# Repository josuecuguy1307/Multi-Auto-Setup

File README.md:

<div align="center">

<picture>
  <source media="(prefers-color-scheme: dark)" srcset="assets/brand/logo-dark.svg">
  
</picture>

**Your computers, working as a team. Your data, on your network.**

</div>

## Works with

Top row: the operating systems. Bottom row: the chats verified end to end so far. Every chat MAS can connect (Claude Desktop, Open WebUI, Muse Code, Claude Code, Codex, OpenCode) is listed under "What you can do with it".

<div align="center">
<picture><source media="(prefers-color-scheme: dark)" srcset="assets/readme/tile-macos-dark.svg"></picture>
<picture><source media="(prefers-color-scheme: dark)" srcset="assets/readme/tile-windows-dark.svg"></picture>
<picture><source media="(prefers-color-scheme: dark)" srcset="assets/readme/tile-linux-dark.svg"></picture>

<picture><source media="(prefers-color-scheme: dark)" srcset="assets/readme/tile-claude-desktop-dark.svg"></picture>
<picture><source media="(prefers-color-scheme: dark)" srcset="assets/readme/tile-open-webui-dark.svg"></picture>
<picture><source media="(prefers-color-scheme: dark)" srcset="assets/readme/tile-muse-code-dark.svg"></picture>
<picture><source media="(prefers-color-scheme: dark)" srcset="assets/readme/tile-claude-code-dark.svg"></picture>

<picture><source media="(prefers-color-scheme: dark)" srcset="assets/readme/tile-codex-dark.svg"></picture>
<picture><source media="(prefers-color-scheme: dark)" srcset="assets/readme/tile-opencode-dark.svg"></picture>
</div>

## Why MAS

You have several computers and several AIs. Today each AI sees one machine, and you are the glue. MAS is the control layer between **you**, **the AI** and **your machines**: one computer coordinates, the others join with your permission, a local model discovers and sets them up, and every decision that matters is yours. The model chooses its actions; code enforces the rules.

**Discover computers. Understand their capabilities. Prepare and equip their AI environments. Bring together models, agents, harnesses and specialized tools. Coordinate different machines securely as one system.**

## What you can do with it

- **Coding and software development** on the computer and coding harness that fit the task.
- **Software installation and environment setup**: analyze a machine, pick an option, approve the plan, install, verify.
- **CSV processing and data analysis** through the catalog task types for data work.
- **Financial reporting and report generation**: describe the work in your own words; the Recommendation Engine finds a suitable environment and asks you one question before anything is created.
- **Work from the chat you already use.** Connect it once (`mas connect`): Claude Desktop, Open WebUI, Muse Code, Claude Code, Codex and OpenCode reach the same MAS tools through MCP (stdio and streamable HTTP). You recognize your machines, answer questions and approve steps there; pairing codes and secrets never pass through a chat.

## Harnesses, matched to the work

A harness is the execution and tool-access environment an agent works inside. MAS keeps a catalog of environments and picks among them by rule, never by opinion:

| Work | Environments in the catalog |
|---|---|
| Coding | `codex`, `opencode`, `pi`, `claude-code`, `muse-code` |
| Local models and data work | `llamacpp-local` (text, code, summarize, extraction, data cleaning, numeric analysis) |
| Provider API | `meta-model-api` |
| General agent work | `goose`; domain skill packs such as the legal contract-review pack |

The **Recommendation Engine** explores tools, models, harnesses and environments for a kind of work: it names a default and an alternative, what is missing, and what could be installed (`mas_install_tool`) after you approve a plan. The **Router** then selects the harness, model, access and computer among the combinations your machines, permissions, privacy level and admission results allow, and records its reasoning. A confidential task is only ever routed to a combination measured on your own paired machines.

Models MAS can run with are profiles, not code: the local actor on each machine and the `muse-glimmer` / `muse-spark` profile names in `config/models.yaml`, with endpoints you supply. Which model runs where is decided from measured memory and fit, and shown to you before anything installs.

## Built with

MAS was built by two coding agents working during its construction, kept separate from the clients and models MAS operates: **Claude Code** (Claude Sonnet) and **Muse Code** (Meta Muse Wonder), including the local-model harness and Open WebUI integration work. **Claude Design** was used for design work, and smaller local Qwen models served as the in-harness actor during development and experiments. Orchestration, decisions, review and verification with the test and conformance suites: the owner, Josué.

## New in this release

| | What | Where to read it |
|---|---|---|
| <picture><source media="(prefers-color-scheme: dark)" srcset="assets/readme/symbols/coordinator-dark.svg"></picture> | **An interactive terminal for `mas`.** Home, Computers, Help, Questions and Progress in plain language, with clear errors and `mas preview` to try the screens with fake computers. Styled from the same single token source as every other surface, and meaning never depends on color alone. | `src/envrec_mas/tui.py`, `tests/test_tui.py` |
| <picture><source media="(prefers-color-scheme: dark)" srcset="assets/readme/symbols/network-dark.svg"></picture> | **One look for every surface.** The logo, colors and 27 pixel symbols come from one file (`src/envrec_style/tokens.json`); the README images, the terminal banner and the Open WebUI cards are drawn from it, and tests fail if one drifts. The banner adapts to the terminal (wide, narrow, compact; truecolor, 256 or 16 colors; shades with `NO_COLOR`; plain text with no escape codes when there is no terminal). | [docs/STYLE.md](docs/STYLE.md) |
| <picture><source media="(prefers-color-scheme: dark)" srcset="assets/readme/symbols/owner-dark.svg"></picture> | **A first-run menu.** `mas` with no arguments in a terminal shows the banner and a short menu for this computer only (role, service, connect Claude Desktop, announce a node). Each step runs the existing command through its own parser, which shows its plan and waits for your typed yes; the menu never answers for you. With no terminal it prints help and exits with code 2, with no prompt. | `src/envrec_mas/menu.py`, `tests/test_menu.py` |
| <picture><source media="(prefers-color-scheme: dark)" srcset="assets/readme/symbols/model-dark.svg"></picture> | **A recommender that checks itself by code.** For a task it has no answer for, it looks for candidate tools and models in public sources. A lead is kept only if code re-checks its license, whether it is archived, its last push, its stars and its domain tags from the page it came from; a rejected one is counted with a typed reason. The task type is chosen by independent picks, and when no two agree the owner is asked one question instead of a guess. A cloud second opinion is used only if you allowed cloud use, only through the node that holds the access, and never for confidential work. The first-run profile also asks which of your subscriptions may be used automatically. Leads stay hypotheses until measured. | [docs/RECOMMENDATION_SPEC.md](docs/RECOMMENDATION_SPEC.md), `tests/test_research_checks.py`, `tests/test_type_choice.py`, `tests/test_slots.py`, `tests/test_subscriptions.py` |
| <picture><source media="(prefers-color-scheme: dark)" srcset="assets/readme/symbols/script-dark.svg"></picture> | **One format for everything the harness says to you.** A title line with a symbol, short sections, numbered options you can answer with a number, a `Next:` line only when something is left to do. Three levels, `brief`, `normal` and `detailed` (`mas config verbosity LEVEL`, or ask in a chat); the commands of a plan or an approval are never shortened, and a test shows the content is the same at every level. A new conformance check (HA11) fails if text that only informs asks you to decide. | `src/envrec_harness/formatter.py`, `tests/test_formatter.py` |
| <picture><source media="(prefers-color-scheme: dark)" srcset="assets/readme/symbols/guard-dark.svg"></picture> | **A voice skill for the chat's own sentences** (`mas-voice`): answer in the person's language, briefly, ask with options, never touch fixed strings. It is handed to the chat when it connects. | `skills/mas-voice`, `tests/test_voice_skill.py` |

## How it works

<picture>
  <source media="(prefers-color-scheme: dark)" srcset="assets/readme/flow-dark.svg">
  
</picture>

| Stage | What goes in | What comes out |
|---|---|---|
| **1 Discover** | a computer on your own subnet | typed facts about it (hardware, system, programs, local AI runtimes), each with the probe that produced it |
| **2 Pair** | a 6-digit code shown on the coordinator, typed once on the new computer | pinned keys on both sides and your recorded yes; nothing else authorizes a computer |
| **3 Analyze** | the facts | what the machine can run, what is missing, options to choose from (you choose) |
| **4 Plan, with approval** | your pick | a plan with the exact commands, sizes and an undo, bound to a hash; you answer once, a changed plan asks again |
| **5 Route** | a task and its sensitivity level | a written rule picks a model and a machine among those allowed for that level; the reason is shown |
| **6 Log** | every event | an append-only, hash-chained log, each line tagged OWNER, MODEL, GUARD or SCRIPT (the router's choice is tagged ROUTER) |

### Features

| | Feature |
|---|---|
| <picture><source media="(prefers-color-scheme: dark)" srcset="assets/readme/symbols/network-dark.svg"></picture> | **One port.** The coordinator listens on one LAN port; nodes listen on none and always dial out. |
| <picture><source media="(prefers-color-scheme: dark)" srcset="assets/readme/symbols/paired-dark.svg"></picture> | **Pairing by key exchange.** A one-time code is the password of a SPAKE2 exchange; mutual TLS with pinned keys; signed messages. |
| <picture><source media="(prefers-color-scheme: dark)" srcset="assets/readme/symbols/model-dark.svg"></picture> | **A model decides, code guards.** One validated action per turn from a closed menu ([spec](docs/HARNESS_SPEC.md)). |
| <picture><source media="(prefers-color-scheme: dark)" srcset="assets/readme/symbols/approved-dark.svg"></picture> | **Approvals with an undo.** Every write shows the exact action and how to undo it, recorded first. |
| <picture><source media="(prefers-color-scheme: dark)" srcset="assets/readme/symbols/local-dark.svg"></picture> | **Local first.** Data stays on your machines unless you allow otherwise. |
| <picture><source media="(prefers-color-scheme: dark)" srcset="assets/readme/symbols/confidential-dark.svg"></picture> | **Sensitivity levels in code.** `public`, `internal`, `confidential`; a confidential task never goes to a cloud model. |
| <picture><source media="(prefers-color-scheme: dark)" srcset="assets/readme/symbols/guard-dark.svg"></picture> | **A conformance suite** (`conformance/`) that encodes the rules, including that a node opens no listening socket. |
| <picture><source media="(prefers-color-scheme: dark)" srcset="assets/readme/symbols/undone-dark.svg"></picture> | **Undo.** A finished setup can be undone as its own approved run. |

## Safety model

- **Nodes open no ports.** The coordinator opens one LAN port (plus, only if you ask, a screen on this computer's loopback).
- **Pairing needs your code and your yes.** A code lives two minutes and allows one attempt.
- **Read-only by default.** Discovery reads; it writes nothing.
- **Every write is approved** with the exact command and its undo, a fresh approval each time.
- **Confidential never leaves your network.** Enforced when the router chooses and at the node's calls, not by a prompt. Cloud models and commercial harnesses count as cloud.
- **Key names only.** Secrets are entered in a hidden window on your computer, stored in the operating system's credential store, and never pass through a chat, a log or a prompt.
- **Your own machines only.** The software never changes a firewall, network profile or router setting; it tells you what to change.
- **Text from the world is data, never instructions.** Generated code runs only in a sandbox that fails closed, and you approve its exact hash before it touches a device.

Details: [docs/NETWORK_CONTRACT.md](docs/NETWORK_CONTRACT.md).

## Install

One installer per operating system. Each installs for one user, with no administrator rights, and installs this program only (no AI models). Nothing is signed, so download the script, read it, then run it. Details, uninstall, service, update and unpair: [docs/INSTALL.md](docs/INSTALL.md).

**macOS and Linux**

```bash
curl -fsSLO https://raw.githubusercontent.com/josuecuguy1307/Multi-Auto-Setup/main/install.sh
less install.sh
sh install.sh
```

**Windows 10 and 11 (PowerShell)**

```powershell
Invoke-WebRequest https://raw.githubusercontent.com/josuecuguy1307/Multi-Auto-Setup/main/install.ps1 -OutFile install.ps1
notepad install.ps1
powershell -ExecutionPolicy Bypass -File .\install.ps1
```

The installers download one pinned release and stop if its SHA-256 differs from the value written in the script. Afterwards: `mas join` on a node, `mas coordinator start --bind ADDRESS` on the coordinator, `mas service install` to start at sign-in, `mas update`, `mas unpair NODE`.

### From a source checkout

Python 3.11 or newer.

```bash
uv venv --python 3.13 .venv && uv pip install --python .venv/bin/python -e .
```

```bash
.venv/bin/python -m pytest conformance
```

## More

- **Harness App standard:** how a chat connects to the harness without being modified: [docs/HARNESS_APP_STANDARD.md](docs/HARNESS_APP_STANDARD.md).
- **Style:** the logo, colors and symbols: [docs/STYLE.md](docs/STYLE.md).
- **Licenses of what is used:** [THIRD_PARTY.md](THIRD_PARTY.md).
- **Portable device (branch `device/v0`):** the key with a physical approval button, its firmware, board and policy gate, what is simulated, emulated or design-only, and how to reproduce every check: [device/README.md](device/README.md).

## License

Licensed under the Apache License, Version 2.0. See LICENSE and NOTICE.

## Hackathon

Built for the Meta Global AI Developer Hackathon, Indie track.

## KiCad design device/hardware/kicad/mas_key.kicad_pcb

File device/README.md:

# MAS portable device (branch device/v0)

A portable device that carries its owner's AI (local model, agent harness, memory). Plugged into someone else's computer, and only
with that computer owner's permission, it connects the AI there without installing anything, inspects the machine read-only, and helps
set up MAS (Multi Auto Setup) on it, one approved write at a time with undo. A small key with a physical button is the only way to
approve a write: the limits live in the key's firmware and in the policy gate, not in the model. Source of truth: `MISSION.md`;
decisions: `DECISIONS.md`; where things stand: `ACCEPTANCE.md` (generated by the oracle) and `HANDOFF.md`.

## Honesty labels

Every result carries one label, in the code, in `ACCEPTANCE.md` and here:

- **SIMULATED**: a Python model on the development machine (for example the key's reference model, the host as a temporary folder).
- **EMULATED**: the real firmware or system running under an emulator or a virtual machine (QEMU, Renode, VMs).
- **DESIGN-ONLY**: a design that passed automatic checks but was never built (the PCB, the enclosure, the secure-boot plan).
- **REAL**: ran on real things (the repository itself, the oracle).

No board has been made. The fabrication files are stamped "NO FABRICAR sin revisión humana" and suffixed `_NO_FABRICAR`; the human
review list is `device/hardware/HUMAN_REVIEW_PCB.md`. Nothing here was tested on the actual key hardware.

**"No trace", defined (D-010).** The device never claims to leave no trace in the absolute. What it aims for, and what P2-ZEROTRACE
will measure, is: "Nothing installed: no service, driver, autostart, PATH change or file outside a declared temp dir removed on exit.
OS-generated residue is limited to an enumerated allowlist of classes" (USB device history, Prefetch and similar records the host's
operating system writes on its own).

## Where things are

| Path | What |
|---|---|
| `src/mas_device/approval.py` | Signed, single-use, expiring approval tokens (guardrail 3) |
| `src/mas_device/keymodel.py` | Python reference model of the key's firmware (SIMULATED) |
| `src/mas_device/gate.py` | The policy gate: the only code that writes to the host, with a fresh approval per write and a recorded undo |
| `src/mas_device/gated.py` | The gate as its own process, reached only through a fixed JSON-lines interface |
| `src/mas_device/log.py` | The append-only, hash-chained audit log |
| `device/firmware/` | The key's firmware in C (`device/firmware/README.md`), its secure-boot design (`device/firmware/SECURE_BOOT.md`) |
| `device/hardware/` | The key board as code: `device/hardware/design.py` is the source, `device/hardware/hwbuild.py` builds everything |
| `device/acceptance/criteria.yaml` | Every acceptance criterion: its tests, the files it covers, its label, its saboteurs |
| `device/tests/` | The tests behind every criterion |
| `device/evals/evaluator/` | Every independent evaluator report, verbatim |
| `scripts/device_accept.py` | The oracle: the only thing that writes `test-results.json` and the status table in `ACCEPTANCE.md` |

## Tools (versions used; reinstall if you change machines)

| Tool | Version | Install | Used by |
|---|---|---|---|
| Python venv | 3.13 | `uv venv .venv` then `uv pip install -e .` | everything |
| zig (`zig cc`) | 0.13.0 | `uv venv runs/toolchain --python 3.13` then `uv pip install --python runs/toolchain/Scripts/python.exe ziglang==0.13.0` | firmware host and emulator builds |
| QEMU (`qemu-system-arm`) | 11.1.0 | `winget install SoftwareFreedomConservancy.QEMU` | P4-FW-EMU |
| Renode (portable) | 1.17.0 | the official zip from github.com/renode/renode, release v1.17.0, unpacked in `runs/toolchain/renode/` | P4-FW-RENODE |
| KiCad (`kicad-cli`, its Python with pcbnew) | 10.0.8 | `winget install KiCad.KiCad` | P5-PCB |

Licenses for all of these are in `THIRD_PARTY.md`. `runs/` is git-ignored: tools and logs never enter the repository.

## Reproduce

One command runs every criterion and rewrites `test-results.json` and the table in `ACCEPTANCE.md`:

```
python scripts/device_accept.py run            # all criteria (about 40 minutes; the board rebuild is most of it)
python scripts/device_accept.py run --id P2-GATE
python scripts/device_accept.py status         # read-only
python scripts/device_accept.py verify         # read-only: fails if any recorded PASS is stale
python scripts/device_accept.py confirm        # the stop condition: clean tree, fresh worktree at HEAD, everything re-run
```

On Windows use `.venv/Scripts/python`; on POSIX `.venv/bin/python`. A criterion passes only if its tests pass, its minimum test count is
met and every saboteur (a deliberate break of the covered code) turns its tests red.

| Criterion | Label | What it shows | Needs |
|---|---|---|---|
| P1-HARNESS | REAL | the oracle treats skips and missing files as FAIL and detects stale results | Python |
| P1-DOCS | REAL | decisions, threat model, guardrail and PCB specs, advisor and reviewer advice are recorded | Python |
| P1-UNIT | SIMULATED | signed approvals, with an independent evaluator's PASS bound to the code's hash | Python |
| P2-GATE | SIMULATED | writes only with a fresh approval for the exact action; undo recorded first | Python |
| P2-LOG | SIMULATED | the audit log detects any edit, cut or reorder against a known head | Python |
| P2-GUARDRAILS | SIMULATED | a scripted malicious model gets zero violations of the ten guardrails | Python |
| P2-PORTABLE | EMULATED | one command (`sh launch.sh`) from a read-only medium in a clean Debian container with no Python and no network; the medium carries its own interpreter and is checked against its manifest; the profiler picks host or device compute from cgroup limits | Docker running; once: `python device/medium/mas_medium_build.py fetch` and `docker pull` of the pinned image |
| P2-ZEROTRACE | EMULATED | the D-010 three-arm diff over whole-filesystem snapshots of clean containers: the session leaves nothing, an approved write changes exactly its files, its undo returns to the session arm; a bad stick's installs are each caught | same as P2-PORTABLE (Docker running, medium cache) |
| P2-FLEET | EMULATED | three containers on an internal network: the host owner types JOIN <fleet>, one press for JOIN_FLEET (checked by the coordinator against the pinned key), one press per setup step, one per undo when leaving; a raw-frame sentinel sees nothing from the peers | same as P2-PORTABLE (Docker running, medium cache) |
| P2-MODEL | EMULATED | the local model answers from the read-only medium | not built yet; needs a local model |
| P2-MEMORY | SIMULATED | portable memory in the open `.mem` bundle format round-trips; at rest it is one scrypt + AES-256-GCM sealed file | Python |
| P2-PAIRING | SIMULATED | the gate accepts only the key paired with the medium (`pairing.json`); the owner sees the session terms at launch; MAS chat approvals absent from the device build | Python |
| P3-INSPECT | SIMULATED | inventory precision >= 0.95 and recall >= 0.90 on four fixture containers whose truth comes from independent tools (dpkg-query, uname, getconf, /sys/module, ioctl, /proc/partitions, the shell); exact on dpkg states, os-release quoting, kernel release and disks | same as P2-PORTABLE (Docker running, medium cache); raw scores in runs/eval/inspect-accuracy.json |
| P3-READONLY | EMULATED | one INSPECT_SESSION press, then a closed set of file-only collectors behind a path allowlist: zero writes by whole-filesystem diff, works on a read-only root, a network sentinel hears nothing, a host's link from an allowed name to a secret is refused; no MAS skill or scanner on the medium | same as P2-PORTABLE (Docker running, medium cache) |
| P3-REPORT | SIMULATED | three files per inspection in the device folder: the full JSON report and a bounded agent view, both checked against closed JSON Schemas (device validator and independent pydantic models agree on every mutation), and the owner's Markdown; hostile host text (terminal escapes, line breaks, bidi) is shown escaped; an invalid report is never written | Python |
| P3-NOCREDS | SIMULATED | hosts planted with secrets in every usual store (shadow, ssh, aws, .env, TLS key, git, browser, gcloud, process environ and cmdline) and inside allowed fields: none appears, raw or encoded, in any output; credential-like values are withheld whole; a stock Debian loses nothing | same as P2-PORTABLE (Docker running, medium cache) |
| P4-FW-HOST | SIMULATED | the firmware rejects replayed, altered and expired approvals; signs only after a press | zig |
| P4-FW-EMU | EMULATED | the same firmware in QEMU gives identical transcripts | zig, QEMU |
| P4-FW-RENODE | EMULATED | the same firmware in Renode gives identical transcripts | zig, Renode |
| P4-SECBOOT | DESIGN-ONLY | the secure-boot and lock design matches the firmware's assumptions | Python |
| P5-PCB | DESIGN-ONLY | ERC, DRC and fabrication checks green, board facts read through pcbnew | KiCad |
| P5-ENCLOSURE | DESIGN-ONLY | a parametric enclosure fits the board by automatic check | Python |
| P6-EVALS | REAL | evals reproducible with one command | not built yet |
| P6-REPO | REAL | this file, `THIRD_PARTY.md`, reproduction instructions | Python |
| P6-PAPER | REAL | the paper regenerates from raw results | not built yet |
| P0-SECRETS | REAL | no credentials anywhere in the tree or its history | git |

The board alone: `python device/hardware/hwbuild.py --out runs/hw/out` (5 to 10 minutes). The firmware alone:
`python device/firmware/build.py`.

## License

Software: see `LICENSE` and `NOTICE`. Hardware (the board and enclosure files): CERN-OHL-S-2.0, chosen by the owner on 2026-11-19 (`LICENSE-HARDWARE.md`, D-014). Earlier proposals (CERN-OHL-P-2.0) and the decision are recorded in `NEEDS_HUMAN.md` and D-014.

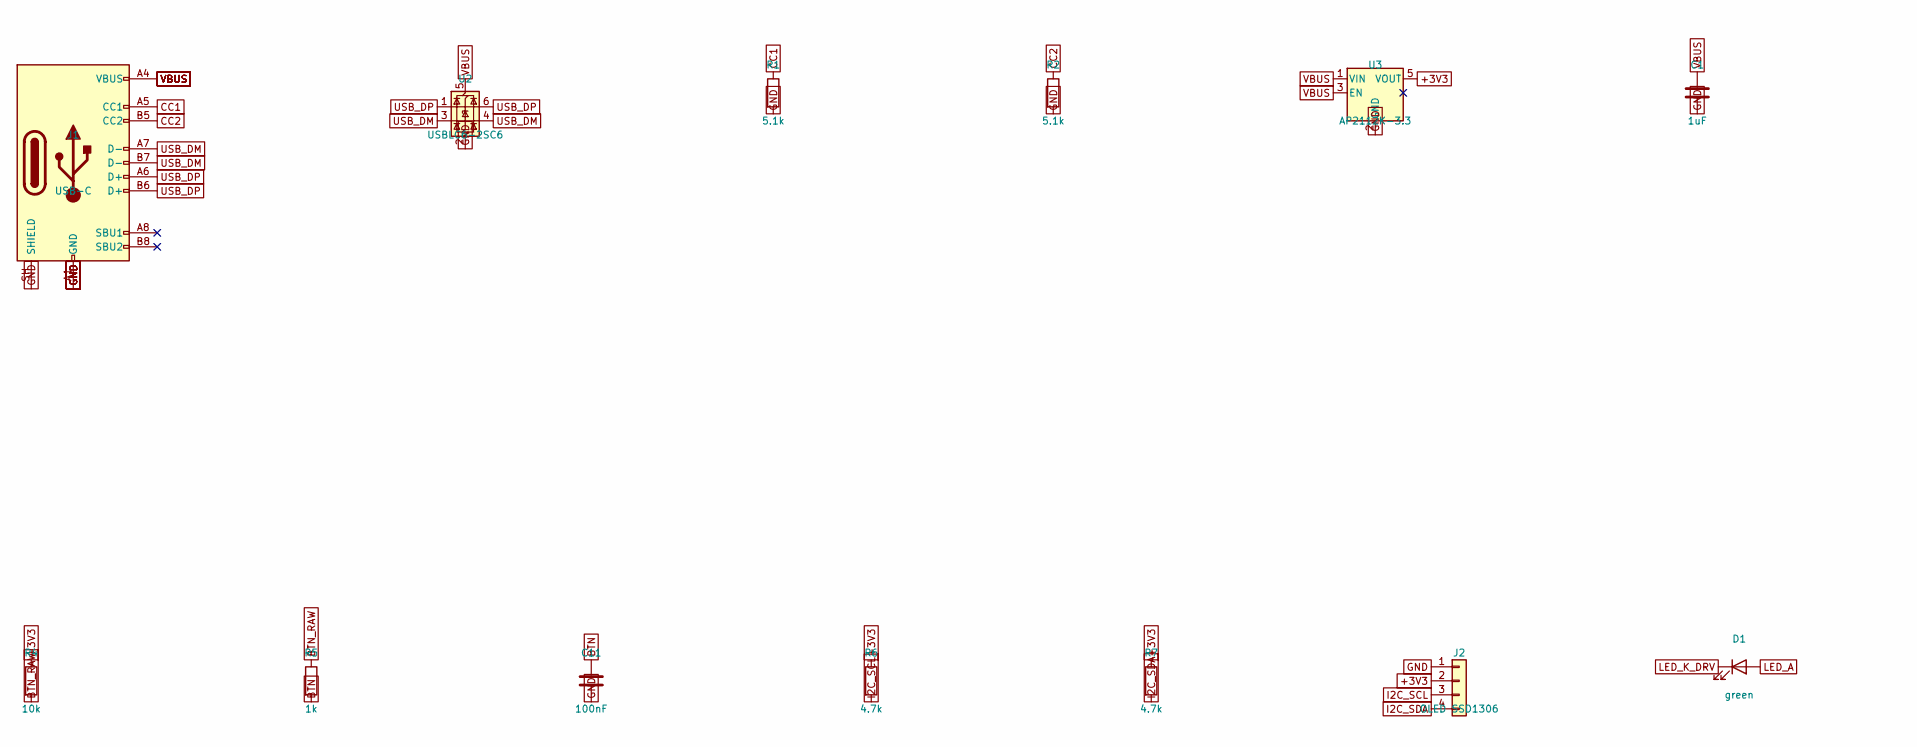
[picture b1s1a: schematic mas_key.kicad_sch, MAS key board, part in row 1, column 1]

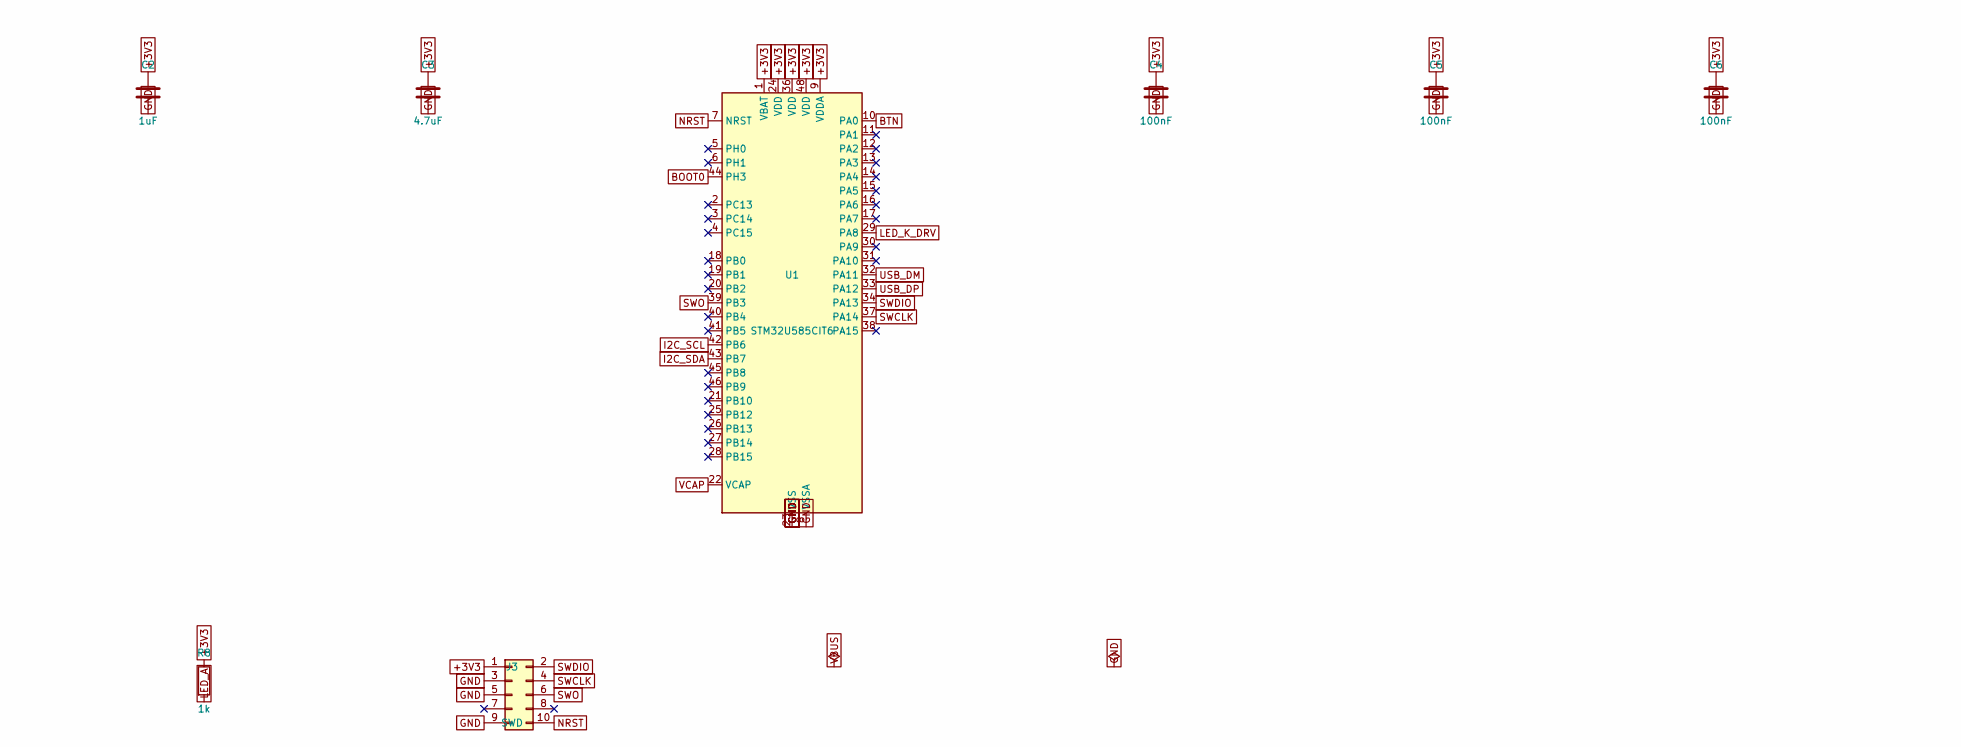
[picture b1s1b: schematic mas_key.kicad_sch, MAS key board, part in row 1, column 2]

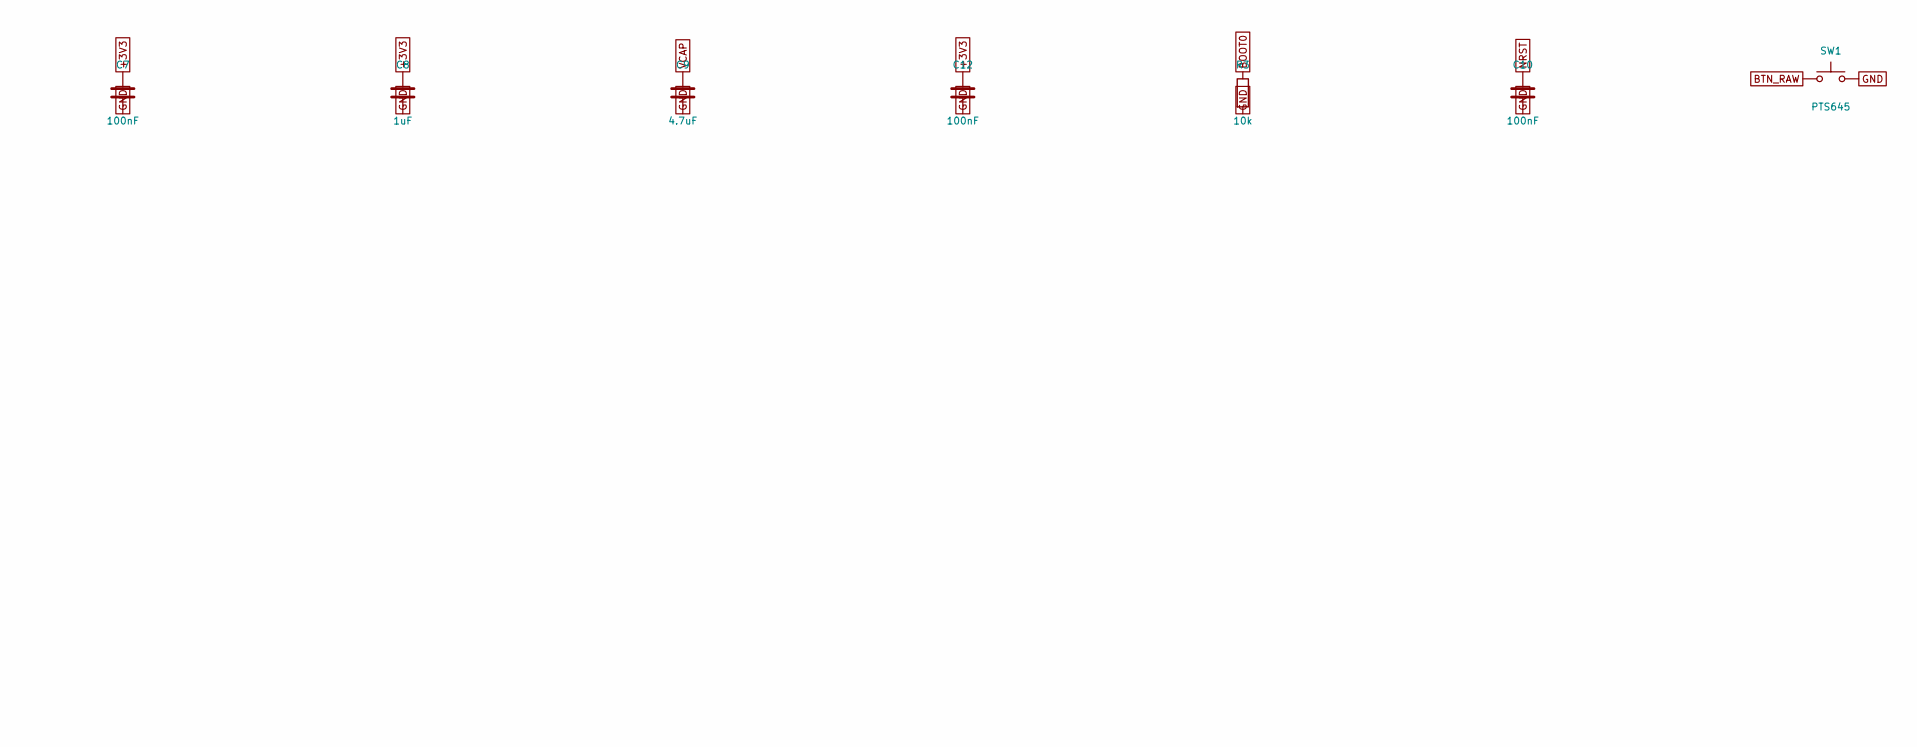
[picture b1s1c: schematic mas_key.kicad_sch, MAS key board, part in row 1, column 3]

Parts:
C1, C2, C8: 1uF; C_0603_1608Metric; MPN CL10A105KB8NNNC
C3, C9: 4.7uF; C_0603_1608Metric; MPN CL10A475KO8NNNC
C4, C5, C6, C7, C10, C11, C12: 100nF; C_0603_1608Metric; MPN CL10B104KB8NNNC
D1: green; LED_0603_1608Metric; MPN LTST-C191KGKT
J1: USB-C; USB_C_Receptacle_GCT_USB4105-xx-A_16P_TopMnt_Horizontal; MPN USB4105-GF-A
J2: OLED SSD1306; PinSocket_1x04_P2.54mm_Vertical; MPN PPTC041LFBN-RC
J3: SWD; PinHeader_2x05_P1.27mm_Vertical_SMD; MPN FTSH-105-01-L-DV-K
R1, R2: 5.1k; R_0603_1608Metric; MPN RC0603FR-075K1L
R3, R4: 10k; R_0603_1608Metric; MPN RC0603FR-0710KL
R5, R8: 1k; R_0603_1608Metric; MPN RC0603FR-071KL
R6, R7: 4.7k; R_0603_1608Metric; MPN RC0603FR-074K7L
SW1: PTS645; SW_SPST_PTS645Sx43SMTR92; MPN PTS645SM43SMTR92LFS
U1: STM32U585CIT6; LQFP-48_7x7mm_P0.5mm; MPN STM32U585CIT6
U2: USBLC6-2SC6; SOT-23-6; MPN USBLC6-2SC6
U3: AP2112K-3.3; SOT-23-5; MPN AP2112K-3.3TRG1

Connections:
+3V3: C2.1, C3.1, C4.1, C5.1, C6.1, C7.1, C8.1, C12.1, J2.2, J3.1, R4.1, R6.1, R7.1, R8.1, U1.1 (VBAT), U1.9 (VDDA), U1.24 (VDD), U1.36 (VDD), U1.48 (VDD), U3.5 (VOUT)
BOOT0: R3.1, U1.44 (PH3)
BTN: C11.1, R5.2, U1.10 (PA0)
BTN_RAW: R4.2, R5.1, SW1.1
CC1: J1.A5 (CC1), R1.1
CC2: J1.B5 (CC2), R2.1
GND: C1.2, C2.2, C3.2, C4.2, C5.2, C6.2, C7.2, C8.2, C9.2, C10.2, C11.2, C12.2, J1.A1 (GND), J1.A12 (GND), J1.B1 (GND), J1.B12 (GND), J1.SH (SHIELD), J2.1, J3.3, J3.5, J3.9, R1.2, R2.2, R3.2, SW1.2, U1.8 (VSSA), U1.23 (VSS), U1.35 (VSS), U1.47 (VSS), U2.2 (GND), U3.2 (GND)
I2C_SCL: J2.3, R6.2, U1.42 (PB6)
I2C_SDA: J2.4, R7.2, U1.43 (PB7)
LED_A: D1.2 (A), R8.2
LED_K_DRV: D1.1 (K), U1.29 (PA8)
NRST: C10.1, J3.10, U1.7 (NRST)
SWCLK: J3.4, U1.37 (PA14)
SWDIO: J3.2, U1.34 (PA13)
SWO: J3.6, U1.39 (PB3)
USB_DM: J1.A7 (D-), J1.B7 (D-), U1.32 (PA11), U2.3 (I/O2), U2.4 (I/O2)
USB_DP: J1.A6 (D+), J1.B6 (D+), U1.33 (PA12), U2.1 (I/O1), U2.6 (I/O1)
VBUS: C1.1, J1.A4 (VBUS), J1.A9 (VBUS), J1.B4 (VBUS), J1.B9 (VBUS), U2.5 (VBUS), U3.1 (VIN), U3.3 (EN)
VCAP: C9.1, U1.22 (VCAP)

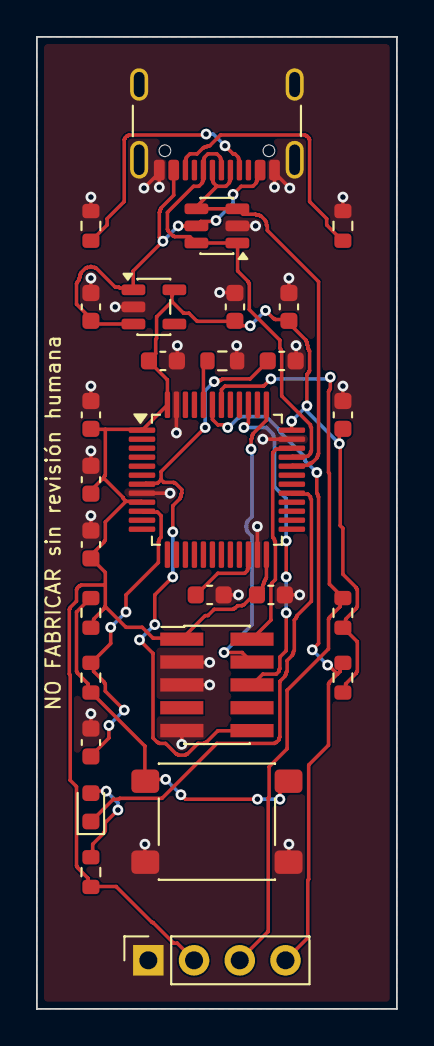
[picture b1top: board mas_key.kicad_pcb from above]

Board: 2 copper layers, 20.0 x 54.0 mm, 28 parts (0 on the bottom side), 19 nets.

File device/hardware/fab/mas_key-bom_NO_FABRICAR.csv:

# NO FABRICAR sin revisión humana
"Reference","Value","Footprint","MPN","Manufacturer","QUANTITY","DNP"
"C1,C2,C8","1uF","Capacitor_SMD:C_0603_1608Metric","CL10A105KB8NNNC","Samsung","3",""
"C3,C9","4.7uF","Capacitor_SMD:C_0603_1608Metric","CL10A475KO8NNNC","Samsung","2",""
"C4-C7,C10-C12","100nF","Capacitor_SMD:C_0603_1608Metric","CL10B104KB8NNNC","Samsung","7",""
"D1","green","LED_SMD:LED_0603_1608Metric","LTST-C191KGKT","Lite-On","1",""
"J1","USB-C","Connector_USB:USB_C_Receptacle_GCT_USB4105-xx-A_16P_TopMnt_Horizontal","USB4105-GF-A","GCT","1",""
"J2","OLED SSD1306","Connector_PinSocket_2.54mm:PinSocket_1x04_P2.54mm_Vertical","PPTC041LFBN-RC","Sullins","1",""
"J3","SWD","Connector_PinHeader_1.27mm:PinHeader_2x05_P1.27mm_Vertical_SMD","FTSH-105-01-L-DV-K","Samtec","1",""
"R1,R2","5.1k","Resistor_SMD:R_0603_1608Metric","RC0603FR-075K1L","Yageo","2",""
"R3,R4","10k","Resistor_SMD:R_0603_1608Metric","RC0603FR-0710KL","Yageo","2",""
"R5,R8","1k","Resistor_SMD:R_0603_1608Metric","RC0603FR-071KL","Yageo","2",""
"R6,R7","4.7k","Resistor_SMD:R_0603_1608Metric","RC0603FR-074K7L","Yageo","2",""
"SW1","PTS645","Button_Switch_SMD:SW_SPST_PTS645Sx43SMTR92","PTS645SM43SMTR92LFS","C&K","1",""
"U1","STM32U585CIT6","Package_QFP:LQFP-48_7x7mm_P0.5mm","STM32U585CIT6","STMicroelectronics","1",""
"U2","USBLC6-2SC6","Package_TO_SOT_SMD:SOT-23-6","USBLC6-2SC6","STMicroelectronics","1",""
"U3","AP2112K-3.3","Package_TO_SOT_SMD:SOT-23-5","AP2112K-3.3TRG1","Diodes Inc","1",""

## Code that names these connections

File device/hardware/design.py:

"""Source of truth for the MAS key board (DESIGN-ONLY; spec: DECISIONS.md A-3, A-1 §6, D-007, D-008).

Everything else is generated from this file: the schematic (gen_sch.py), the netlist (kicad-cli), the board (gen_pcb.py, from the netlist),
the fabrication outputs and the BOM. MCU pins are named, never numbered: the numbers come from KiCad's stock symbol, so the human review
reduces to "stock symbol against the datasheet" (HUMAN_REVIEW_PCB.md item 1).

NO FABRICAR sin revisión humana.
"""

from __future__ import annotations

from dataclasses import dataclass, field

BOARD_W, BOARD_H = 20.0, 54.0          # mm; long axis = y, USB-C mouth at y = 0 (A-3 said 48; the OLED socket needs the length)
SILK_TEXT_X = 0.9                       # the stamp runs along this strip, 0.9 mm from the left edge (right edge on B.SilkS); keep parts out of it
STAMP = "NO FABRICAR sin revisión humana"
BOM_SNAPSHOT_DATE = "2026-11-17"  # parts list frozen on this date; no live distributor lookup was made (bom_snapshot.json)


@dataclass(frozen=True)
class Part:
    ref: str
    lib_id: str
    footprint: str
    value: str
    mpn: str
    manufacturer: str
    pins: dict = field(default_factory=dict)  # pin NAME (or number for passives/connectors) -> net; unlisted pins are no-connect
    at: tuple = (0.0, 0.0, 0.0)               # board placement (x, y, rotation) in mm, origin at the board's top-left corner
    dnp: bool = False


R0603, C0603 = "Resistor_SMD:R_0603_1608Metric", "Capacitor_SMD:C_0603_1608Metric"


def R(ref, value, a, b, at, mpn):
    return Part(ref, "Device:R", R0603, value, mpn, "Yageo", {"1": a, "2": b}, at)


def C(ref, value, a, b, at, mpn):
    return Part(ref, "Device:C", C0603, value, mpn, "Samsung", {"1": a, "2": b}, at)


# The MCU's pins by name. Names must match the stock symbol's pin names exactly; gen_sch.py refuses to build otherwise.
MCU_PINS = {
    "PA11": "USB_DM", "PA12": "USB_DP",
    "PA13": "SWDIO", "PA14": "SWCLK", "PB3": "SWO",
    "PB6": "I2C_SCL", "PB7": "I2C_SDA",
    "PA0": "BTN", "PA8": "LED_K_DRV",
    "PH3": "BOOT0", "NRST": "NRST",
    "VDD": "+3V3", "VDDA": "+3V3", "VBAT": "+3V3",  # the stock LQFP48 symbol names pin 36 VDD (no VDDUSB): UNVERIFIED
    "VSS": "GND", "VSSA": "GND",
    "VCAP": "VCAP",
}

PARTS = [
    # ---- USB-C, ESD, regulator (top of the board) ----
    Part("J1", "Connector:USB_C_Receptacle_USB2.0_16P", "Connector_USB:USB_C_Receptacle_GCT_USB4105-xx-A_16P_TopMnt_Horizontal",
         "USB-C", "USB4105-GF-A", "GCT",
         {"VBUS": "VBUS", "GND": "GND", "SHIELD": "GND", "CC1": "CC1", "CC2": "CC2", "D+": "USB_DP", "D-": "USB_DM"}, (10.0, 3.72, 180.0)),
    Part("U2", "Power_Protection:USBLC6-2SC6", "Package_TO_SOT_SMD:SOT-23-6", "USBLC6-2SC6", "USBLC6-2SC6", "STMicroelectronics",
         {"I/O1": "USB_DP", "I/O2": "USB_DM", "VBUS": "VBUS", "GND": "GND"}, (10.0, 10.5, 180.0)),  # turned so D- exits above D+:
    # the two chains J1 -> U2 -> U1 then nest without crossing on the top layer (U1's D+ pin is above its D- pin; board evaluator run 2)
    R("R1", "5.1k", "CC1", "GND", (3.0, 10.5, 90.0), "RC0603FR-075K1L"),
    R("R2", "5.1k", "CC2", "GND", (17.0, 10.5, 90.0), "RC0603FR-075K1L"),
    Part("U3", "Regulator_Linear:AP2112K-3.3", "Package_TO_SOT_SMD:SOT-23-5", "AP2112K-3.3", "AP2112K-3.3TRG1", "Diodes Inc",
         {"VIN": "VBUS", "EN": "VBUS", "GND": "GND", "VOUT": "+3V3"}, (6.5, 15.0, 0.0)),
    C("C1", "1uF", "VBUS", "GND", (3.0, 15.0, 90.0), "CL10A105KB8NNNC"),
    C("C2", "1uF", "+3V3", "GND", (11.0, 15.0, 90.0), "CL10A105KB8NNNC"),
    C("C3", "4.7uF", "+3V3", "GND", (14.0, 15.0, 90.0), "CL10A475KO8NNNC"),
    # ---- MCU and its supply pins (centre) ----
    Part("U1", "MCU_ST_STM32U5:STM32U585CITx", "Package_QFP:LQFP-48_7x7mm_P0.5mm", "STM32U585CIT6", "STM32U585CIT6",
         "STMicroelectronics", MCU_PINS, (10.0, 24.6, 0.0)),
    C("C4", "100nF", "+3V3", "GND", (3.0, 21.0, 90.0), "CL10B104KB8NNNC"),
    C("C5", "100nF", "+3V3", "GND", (17.0, 21.0, 90.0), "CL10B104KB8NNNC"),
    C("C6", "100nF", "+3V3", "GND", (3.0, 24.6, 90.0), "CL10B104KB8NNNC"),
    C("C7", "100nF", "+3V3", "GND", (13.0, 31.0, 0.0), "CL10B104KB8NNNC"),
    C("C8", "1uF", "+3V3", "GND", (3.0, 28.2, 90.0), "CL10A105KB8NNNC"),
    C("C9", "4.7uF", "VCAP", "GND", (9.6, 31.0, 0.0), "CL10A475KO8NNNC"),
    C("C12", "100nF", "+3V3", "GND", (7.0, 18.0, 0.0), "CL10B104KB8NNNC"),  # pin 48 VDD: one 100 nF per supply pin (A-3, evaluator P5 run 1)
    R("R3", "10k", "BOOT0", "GND", (10.3, 18.0, 0.0), "RC0603FR-0710KL"),
    C("C10", "100nF", "NRST", "GND", (13.6, 18.0, 0.0), "CL10B104KB8NNNC"),
    # ---- button with RC and pull-up ----
    Part("SW1", "Switch:SW_Push", "Button_Switch_SMD:SW_SPST_PTS645Sx43SMTR92", "PTS645", "PTS645SM43SMTR92LFS", "C&K",
         {"1": "BTN_RAW", "2": "GND"}, (10.0, 43.6, 0.0)),
    R("R4", "10k", "+3V3", "BTN_RAW", (3.0, 32.0, 90.0), "RC0603FR-0710KL"),
    R("R5", "1k", "BTN_RAW", "BTN", (3.0, 35.6, 90.0), "RC0603FR-071KL"),
    C("C11", "100nF", "BTN", "GND", (3.0, 39.2, 90.0), "CL10B104KB8NNNC"),
    # ---- I2C display socket, pull-ups, LED, SWD ----
    R("R6", "4.7k", "+3V3", "I2C_SCL", (17.0, 32.0, 90.0), "RC0603FR-074K7L"),
    R("R7", "4.7k", "+3V3", "I2C_SDA", (17.0, 35.6, 90.0), "RC0603FR-074K7L"),
    Part("J2", "Connector_Generic:Conn_01x04", "Connector_PinSocket_2.54mm:PinSocket_1x04_P2.54mm_Vertical", "OLED SSD1306",
         "PPTC041LFBN-RC", "Sullins", {"1": "GND", "2": "+3V3", "3": "I2C_SCL", "4": "I2C_SDA"}, (6.19, 51.3, 90.0)),
    Part("D1", "Device:LED", "LED_SMD:LED_0603_1608Metric", "green", "LTST-C191KGKT", "Lite-On", {"K": "LED_K_DRV", "A": "LED_A"}, (3.0, 42.8, 90.0)),
    R("R8", "1k", "+3V3", "LED_A", (3.0, 46.4, 90.0), "RC0603FR-071KL"),
    Part("J3", "Connector_Generic:Conn_02x05_Odd_Even", "Connector_PinHeader_1.27mm:PinHeader_2x05_P1.27mm_Vertical_SMD", "SWD",
         "FTSH-105-01-L-DV-K", "Samtec",
         {"1": "+3V3", "2": "SWDIO", "3": "GND", "4": "SWCLK", "5": "GND", "6": "SWO", "9": "GND", "10": "NRST"}, (10.0, 36.0, 0.0)),
]

# Nets that only exist as power and that PWR_FLAG must mark as driven (their source is outside the schematic: the USB host).
POWER_FLAGS = ["VBUS", "GND"]

# MCU pins that must exist on the symbol and stay unconnected (no crystal: HSI48 + CRS).
EXPECTED_NO_CONNECT = ["PH0", "PH1", "PC14", "PC15"]

UNVERIFIED = [
    "Every STM32U585CIT6 LQFP48 pin number (taken from KiCad's stock symbol, not checked against DS13086).",
    "VCAP on the LDO (non-Q) STM32U585: presence, count and value (AN5373).",
    "Crystal-less USB FS with HSI48 + CRS on STM32U585 (advisor: confident, not checked against RM0456).",
    "USB-C J1 symbol/footprint names and the GCT USB4105 land pattern.",
    "OLED module pin order (GND/VCC order varies by vendor) and whether the module already carries I2C pull-ups.",
    "AP2112K-3.3 dropout and thermal at worst-case VBUS; VDDA tied to +3V3 without a ferrite (ADC unused).",
    "USB D+/D- routed without impedance control.",
    "Pin 36: the stock LQFP48 symbol names it VDD (no VDDUSB pin); check DS13086 whether it is VDDUSB. Here it is tied to +3V3 with its own 100 nF.",
]

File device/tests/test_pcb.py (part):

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    """Every supply pin of U1 is on a net with capacitors to GND, at least one per supply pin on that net."""
    errors = []
    u1 = next(p for p in design.PARTS if p.ref == "U1")
    supply = [n for k, n in u1.pins.items() if k.startswith(("VDD", "VBAT", "VCAP"))]
    for net in sorted(set(supply)):
        pins = len([r for r in nets.get(net, set()) if r[0] == "U1"])
        caps = {r for r in refs_on(nets, net, "C") if two_pin_between(nets, r, net, "GND")}
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    nodes = nets["BTN"]
    assert len([n for n in nodes if n[0] == "U1"]) == 1
    assert {r for r, _ in nodes if r[0] in "UJ" and r != "U1"} == set()
    assert two_pin_between(nets, "R4", "+3V3", "BTN_RAW") and value_of("R4") == "10k"
    assert refs_on(nets, "BTN_RAW", "SW") == {"SW1"} and two_pin_between(nets, "SW1", "BTN_RAW", "GND")


def test_usb_c_cc_pins_each_have_their_own_5k1_to_ground(nets):
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    for n in sec(sec(doc, "nets")[0], "net"):
        for node in sec(n, "node"):
            pin, func = val(node, "pin"), val(node, "pinfunction")
            func = func[: -len(pin) - 1] if func.endswith("_" + pin) else func  # KiCad 10 suffixes the pin number: PA12_33 -> PA12
            out.append((val(n, "name"), val(node, "ref"), pin, func, val(node, "pintype")))
    values = {val(c, "ref"): val(c, "value") for c in sec(sec(doc, "components")[0], "comp")}
    return out, values
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

def test_the_netlist_is_right_pin_by_pin(pins):
    assert net_of(pins, "U1", "PA12") == ["USB_DP"] and net_of(pins, "U1", "PA11") == ["USB_DM"]
    for p in ("A6", "B6"):
        assert net_of(pins, "J1", number=p) == ["USB_DP"], p
    for p in ("A7", "B7"):
        assert net_of(pins, "J1", number=p) == ["USB_DM"], p
    assert set(net_of(pins, "U2", "I/O1")) == {"USB_DP"} and set(net_of(pins, "U2", "I/O2")) == {"USB_DM"}
    assert net_of(pins, "U1", "PB6") == ["I2C_SCL"] and net_of(pins, "U1", "PB7") == ["I2C_SDA"]
    assert net_of(pins, "U1", "PA0") == ["BTN"] and net_of(pins, "U1", "PH3") == ["BOOT0"]
    for f in ("PH0", "PH1", "PC14", "PC15"):
        assert net_of(pins, "U1", f)[0].startswith("unconnected-"), f

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    j2 = sorted(n for n, r, p, f, _ in pins[0] if r == "J2")
    if j2 != sorted(["GND", "+3V3", "I2C_SCL", "I2C_SDA"]):
        v.append(f"J2 carries {j2}, not GND, +3V3, I2C_SCL and I2C_SDA once each")
    for net, func in (("I2C_SCL", "PB6"), ("I2C_SDA", "PB7")):
        if _one(pins, "U1", func) != net or "J2" not in {r for r, _ in on(net)}:
            v.append(f"{net} does not join U1.{func} to J2")
    bulk = sum(farads(pins[1][c]) for c in _between(pins, "+3V3", "GND", "C") if c in pins[1] and re.fullmatch(r"[\d.]+[pnu]?F", pins[1][c]))
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    for ref, func, net in (("U3", "VIN", "VBUS"), ("U3", "VOUT", "+3V3"), ("U1", "VDDA", "+3V3")):
        if not big_cap_near(ref, func, net):
            v.append(f"no >= 1 uF capacitor within 5 mm of {ref}.{func}")
    if _one(pins, "SW1", number="1") != "BTN_RAW" or _one(pins, "SW1", number="2") != "GND":
        v.append("SW1 is not between BTN_RAW and GND")
    for a, b, prefix, parse, want, what in (("+3V3", "BTN_RAW", "R", ohms, 10e3, "button pull-up 10k"),
                                            ("BTN_RAW", "BTN", "R", ohms, 1e3, "button series 1k"),
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        refs = _between(pins, a, b, prefix)
        if len(refs) != 1 or not _value_is(pins, refs[0], parse, want):
            v.append(what)
    if _one(pins, "U1", "PA0") != "BTN":
        v.append("U1.PA0 is not BTN")
    k, a = _one(pins, "D1", "K"), _one(pins, "D1", "A")
    if k is None or k != _one(pins, "U1", "PA8"):
        v.append("D1 cathode is not driven by U1.PA8")
    led_r = _between(pins, "+3V3", a, "R") if a else []
    if len(led_r) != 1 or not _value_is(pins, led_r[0], ohms, 1e3):
        v.append("D1 anode has no 1k to +3V3")
    for num, func in (("2", "PA13"), ("4", "PA14"), ("6", "PB3"), ("10", "NRST")):
        if _one(pins, "J3", number=num) is None or _one(pins, "J3", number=num) != _one(pins, "U1", func):
            v.append(f"J3.{num} is not U1.{func}")
    if _one(pins, "J3", number="1") != "+3V3" or any(_one(pins, "J3", number=n) != "GND" for n in ("3", "5", "9")):
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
